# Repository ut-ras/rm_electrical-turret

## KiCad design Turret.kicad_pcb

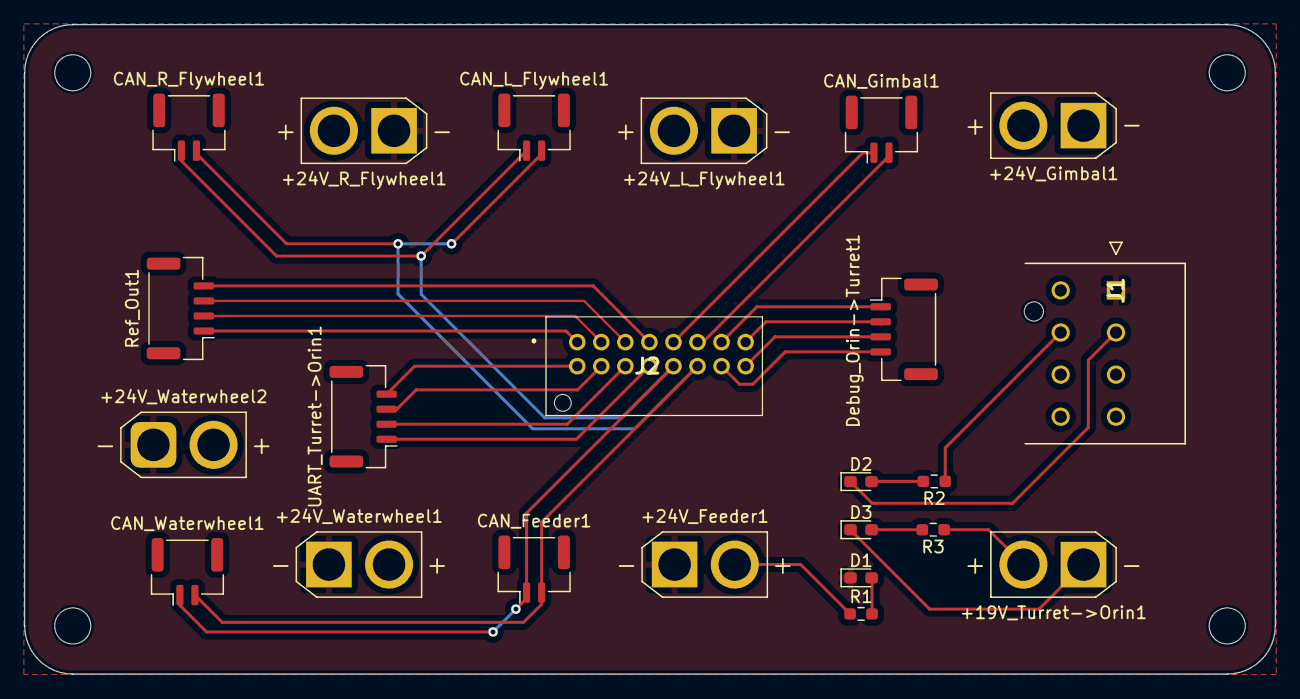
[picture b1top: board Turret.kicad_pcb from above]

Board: 2 copper layers, 104.0 x 54.0 mm, 27 parts (0 on the bottom side), 25 nets.

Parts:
+19V_Turret->Orin1, +24V_Feeder1, +24V_Gimbal1, +24V_L_Flywheel1, +24V_R_Flywheel1, +24V_Waterwheel1, +24V_Waterwheel2: Conn_01x02_Pin; AMASS_XT30U-F_1x02_P5.0mm_Vertical
CAN_Feeder1: Conn_01x02_Pin; JST_GH_BM02B-GHS-TBT_1x02-1MP_P1.25mm_Vertical
CAN_Gimbal1: Conn_01x02_Pin; JST_GH_BM02B-GHS-TBT_1x02-1MP_P1.25mm_Vertical
CAN_L_Flywheel1: Conn_01x02_Pin; JST_GH_BM02B-GHS-TBT_1x02-1MP_P1.25mm_Vertical
CAN_R_Flywheel1: Conn_01x02_Pin; JST_GH_BM02B-GHS-TBT_1x02-1MP_P1.25mm_Vertical
CAN_Waterwheel1: Conn_01x02_Pin; JST_GH_BM02B-GHS-TBT_1x02-1MP_P1.25mm_Vertical
D1, D2, D3: 150060YS75000; LED_0603_1608Metric_Pad1.05x0.95mm_HandSolder
Debug_Orin->Turret1: Conn_01x04_Pin; JST_GH_BM04B-GHS-TBT_1x04-1MP_P1.25mm_Vertical
H1, H2, H3, H4: MountingHole; MountingHole_3mm
J1: 172298-1108; 172298-YY08
J2: 501645-1620; 5016451620
R1, R2, R3: 1k; R_0603_1608Metric_Pad0.98x0.95mm_HandSolder
Ref_Out1: Conn_01x04_Pin; JST_GH_BM04B-GHS-TBT_1x04-1MP_P1.25mm_Vertical
UART_Turret->Orin1: Conn_01x04_Pin; JST_GH_BM04B-GHS-TBT_1x04-1MP_P1.25mm_Vertical

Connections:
/CAN1+: CAN_Gimbal1.2, J2.11
/CAN1-: CAN_Gimbal1.1, J2.9
/CAN2+: CAN_Feeder1.2, CAN_L_Flywheel1.2, CAN_R_Flywheel1.2, CAN_Waterwheel1.2, J2.12
/CAN2-: CAN_Feeder1.1, CAN_L_Flywheel1.1, CAN_R_Flywheel1.1, CAN_Waterwheel1.1, J2.10
/Gimbal_{+24V}: +24V_Gimbal1.2, J1.6, R2.1
/Gimbal_{GND}: +24V_Gimbal1.1, D2.1 (K), J1.2
/OrinPWR_{+19V}: +19V_Turret->Orin1.2, J1.7, R3.1
/OrinPWR_{GND}: +19V_Turret->Orin1.1, D3.1 (K), J1.3
/Ref_{CAN}+: J2.5, Ref_Out1.3
/Ref_{CAN}-: J2.3, Ref_Out1.2
/Ref_{GND}: J2.1, Ref_Out1.1
/Ref_{PWR}: J2.7, Ref_Out1.4
/SWD_{3V3}: Debug_Orin->Turret1.4, J2.14
/SWD_{GND}: Debug_Orin->Turret1.1, J2.13
/SWD_{SWCLK}: Debug_Orin->Turret1.3, J2.16
/SWD_{SWDIO}: Debug_Orin->Turret1.2, J2.15
/Shooter_{+24V}: +24V_Feeder1.2, +24V_L_Flywheel1.2, +24V_R_Flywheel1.2, +24V_Waterwheel1.2, +24V_Waterwheel2.2, J1.5, R1.1
/Shooter_{GND}: +24V_Feeder1.1, +24V_L_Flywheel1.1, +24V_R_Flywheel1.1, +24V_Waterwheel1.1, +24V_Waterwheel2.1, D1.1 (K), J1.1
/UART_{3V3}: J2.2, UART_Turret->Orin1.4
/UART_{GND}: J2.8, UART_Turret->Orin1.1
/UART_{RX}: J2.4, UART_Turret->Orin1.3
/UART_{TX}: J2.6, UART_Turret->Orin1.2
unnamed: D1.2 (A), R1.2
unnamed: D2.2 (A), R2.2
unnamed: D3.2 (A), R3.2

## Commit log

2023-09-29 add Turret
2023-09-29 Add turret schematic
2023-09-29 Add gitignore
2023-09-29 Update schematic
2023-09-29 Add pcb
2023-10-07 Added footprint for aviator
2023-10-14 Wired to connector
2023-10-21 added power connector
2023-10-28 Update turret
2023-11-04 Updated PCB to use unified power 6 pin, added 2 1x2 connectors
2023-11-18 Mostly finished turret schematic
2023-11-18 fixed gnds on sabre connector
2023-11-18 Fixed 24V on sabre connector
2023-12-20 turret dimensions
2024-01-19 Add trace
2024-01-27 Turret change :)
2024-01-27 Update library location
2024-02-03 Added 8 pin connector, 1-4 gnd and 5-8 +24V
2024-02-10 Added 8 pin, ref system connection not needed?
2024-02-17 Correct voltages
2024-02-17 Add footprints
2024-02-23 Fix CAN and change schematic
2024-02-24 Initial layout of footprints on pcb (not final)
2024-03-01 Fixed net names in schematic, initial pcb layout
2024-03-02 Adding new ref system, other push now deprecated
2024-03-06 New layout, test points not final
2024-03-08 Added connections to test points, silkscreens need to be renamed.
2024-03-09 Tried to fix footprints, also changed to traces for testpoints
2024-03-22 New CAN Line, cleaned up schematic, changed pcb
2024-03-24 Added gerber & drill files, and zip for them
2024-03-26 Added 3d model
2024-03-29 Changed symbol fields
2024-03-29 Added the xlsx
2024-11-23 added hierarchial labels for input/output characteristics
2024-11-29 Cleaned up hierarchical labels
2024-12-03 Prepped turret sch for 2x8 molex monolithic conn change
2025-01-08 Added a 16 input connector
2025-01-27 XT30 outputs to ESCs rotated
2025-02-21 Fixed 16-pin and 8-pin netnames for correct connections, updated gerbers
2025-03-08 Added internal connection for ref ports and distiniguished i/o
2025-03-20 Updated fab files
2025-03-21 Added project-level library
2025-03-22 Update fp/sym tables
2025-04-20 Cleaned up hiearchical labels and local labels
2026-01-23 Prepped for work
2026-05-27 Added UV LED connection
